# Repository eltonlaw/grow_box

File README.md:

## Setup

```
git submodule update --init --recursive
```

Use bear to generate `compile_commands.json`

```
bear -- make
```

## Hardware

### Relay PCB

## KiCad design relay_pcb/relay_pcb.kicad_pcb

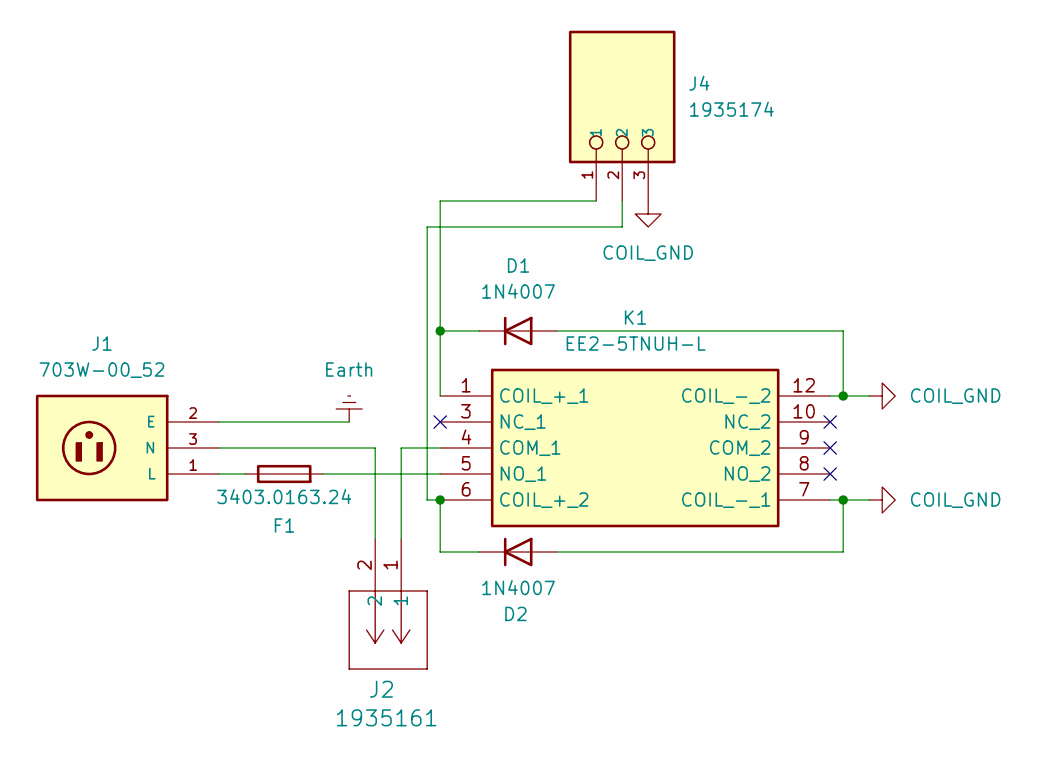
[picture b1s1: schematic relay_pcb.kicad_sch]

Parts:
D1, D2: 1N4007; D_DO-41_SOD81_P7.62mm_Horizontal
F1: 3403.0163.24; Fuse_2010_5025Metric
J1: 703W-00_52; QUALTEK_703W-00_52; PARTREV B
J2: 1935161; CONN_1935161_PXC
J4: 1935174; CONN_1935174_PXC
K1: EE2-5TNUH-L; EE25TNU; Manufacturer_Part_Number EE2-5TNUH-L; Mouser Part Number 80-EE2-5TNUH-L

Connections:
COIL_GND: D1.2 (A), D2.2 (A), J4.3, K1.7 (COIL_-_1), K1.12 (COIL_-_2)
Earth: J1.2 (E)
unnamed: D1.1 (K), J4.1, K1.1 (COIL_+_1)
unnamed: D2.1 (K), J4.2, K1.6 (COIL_+_2)
unnamed: F1.1, J1.1 (L)
unnamed: J1.3 (N), J2.2
unnamed: J2.1, K1.4 (COM_1)
unnamed: F1.2, K1.5 (NO_1)

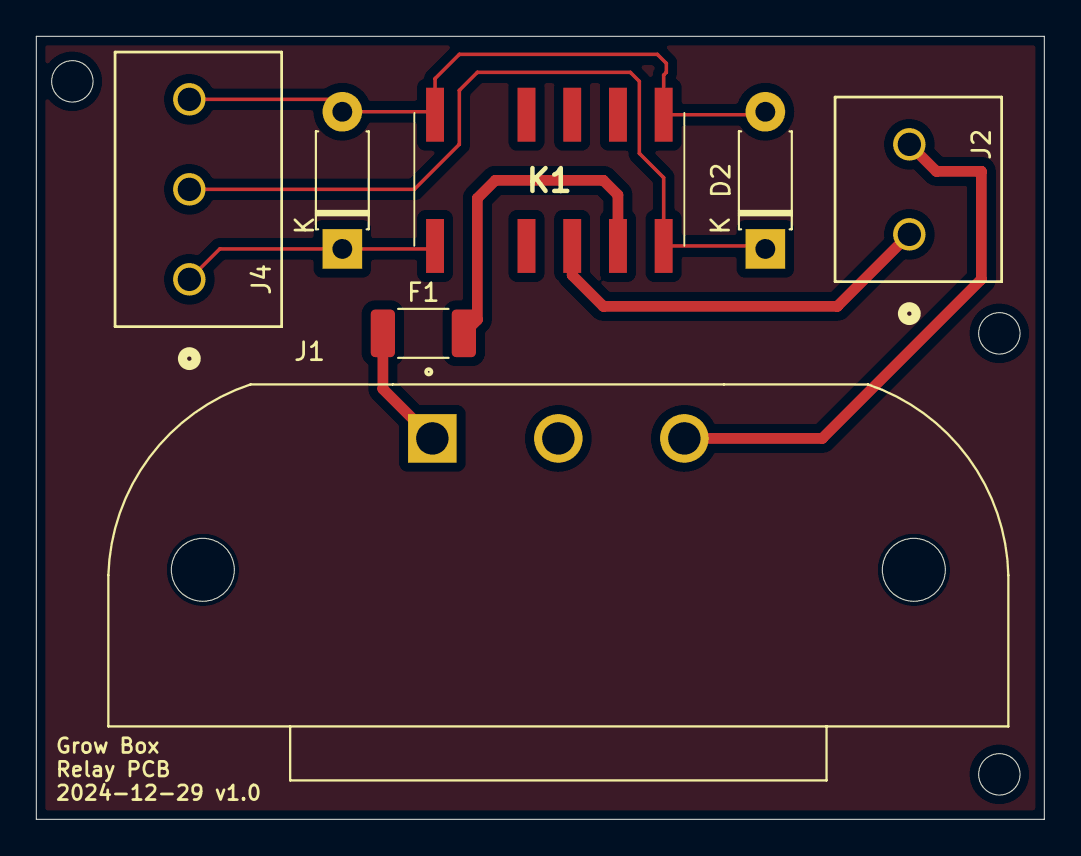
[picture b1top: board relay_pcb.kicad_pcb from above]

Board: 4 copper layers, 56.0 x 43.5 mm, 7 parts (0 on the bottom side), 7 nets.

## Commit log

2024-05-11 feat: add stm32cubeg0 as submodule
2024-05-11 init: add .gitignore and linker script
2024-05-12 docs: add git submodule init
2024-05-26 feat: add lib
2024-05-27 feat: add openocd and gdb interface
2024-05-27 feat: add gdb-tui command
2024-05-27 add .gdbinit
2024-05-29 add linker map generation
2024-06-10 fix: properly link sections to right addr locations
2024-06-13 implement logging interface
2024-06-14 fix: properly disable log subsystems
2024-06-14 link CMSIS to libstm32g0 custom lib
2024-06-14 GPIOA RCC setup
2024-06-15 feat: working blinky
2024-06-15 feat: use atomic ops through BSRR over ODR
2024-06-15 init kicad project
2024-06-16 fix: add SystemCoreClockUpdate() call
2024-06-21 kicad: expose swd pins as ARM-JTAG-10
2024-07-18 fix: obj compile should be one by one
2024-12-18 kicad: add C1 value
2024-12-18 kicad: add usb-c symbol and 5V source
2024-12-26 split into relay and controller pcb
2024-12-30 kicad: relay pcb board for turning on lighbulb 120VAC with +5V
2025-01-04 kicad: add status LED
2025-01-04 chore: refactor gpio utils
2025-01-13 link STM32 vendor HAL
2025-02-10 switch to CMake
